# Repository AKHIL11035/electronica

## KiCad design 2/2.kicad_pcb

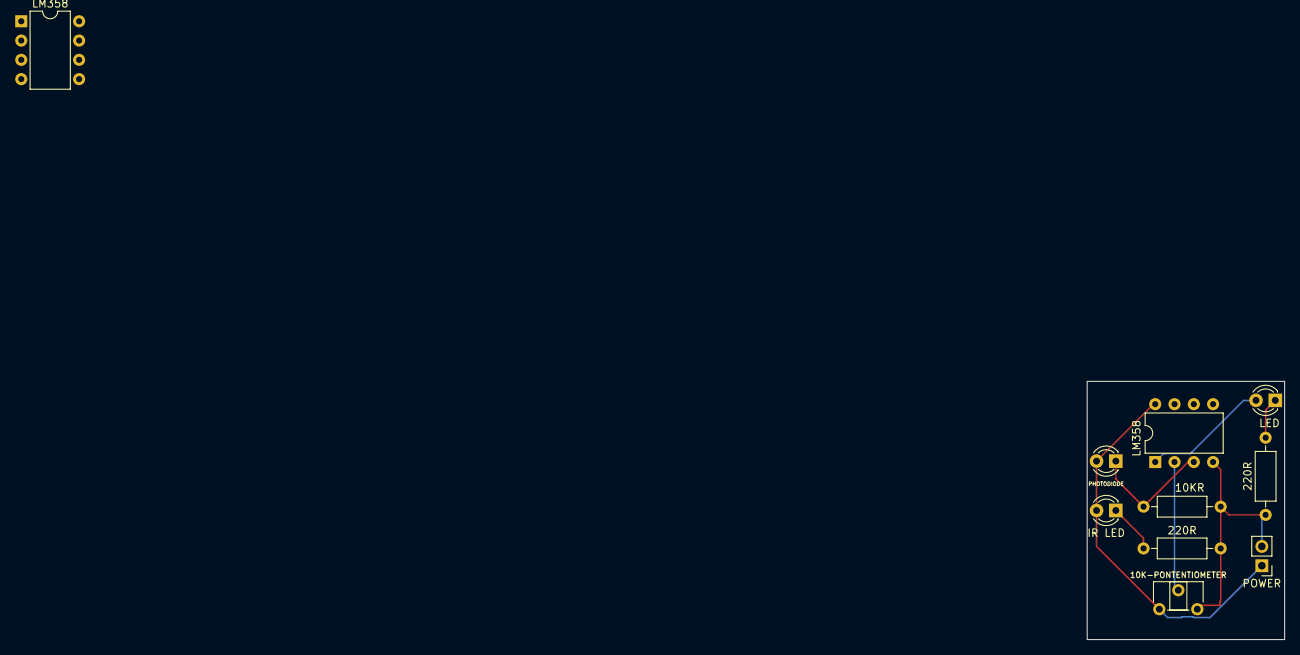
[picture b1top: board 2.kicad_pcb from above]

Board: 2 copper layers, 26.0 x 34.0 mm, 10 parts (0 on the bottom side), 7 nets.

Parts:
10K-PONTENTIOMETER: 10K; Potentiometer_ACP_CA6-H2,5_Horizontal
10KR: 10K; R_Axial_DIN0207_L6.3mm_D2.5mm_P10.16mm_Horizontal
220R, 220R#2: 220; R_Axial_DIN0207_L6.3mm_D2.5mm_P10.16mm_Horizontal
IR LED: IR204A; LED_D3.0mm_Clear
LED: LED; LED_D3.0mm_IRBlack
LM358, LM358#2: LM358; DIP-8_W7.62mm
PHOTODIODE: D_Photo; LED_D3.0mm_IRBlack
POWER: Conn_01x02_Pin; PinHeader_1x02_P2.54mm_Vertical

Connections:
unnamed: 10K-PONTENTIOMETER.1, IR LED.2 (A), LM358#2.8 (V+), PHOTODIODE.2 (A), POWER.1
unnamed: 220R#2.1, IR LED.1 (K)
unnamed: LED.2 (A), LM358#2.1
unnamed: 220R.2, LED.1 (K)
unnamed: 10KR.1, LM358#2.3 (+), PHOTODIODE.1 (K)
unnamed: 10K-PONTENTIOMETER.3, 10KR.2, 220R.1, 220R#2.2, LM358#2.4 (V-), POWER.2
unnamed: 10K-PONTENTIOMETER.2, LM358#2.2 (-)
